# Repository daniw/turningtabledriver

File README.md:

turningtabledriver
==================

Full bridge driver for a dc motor driving a turning table.

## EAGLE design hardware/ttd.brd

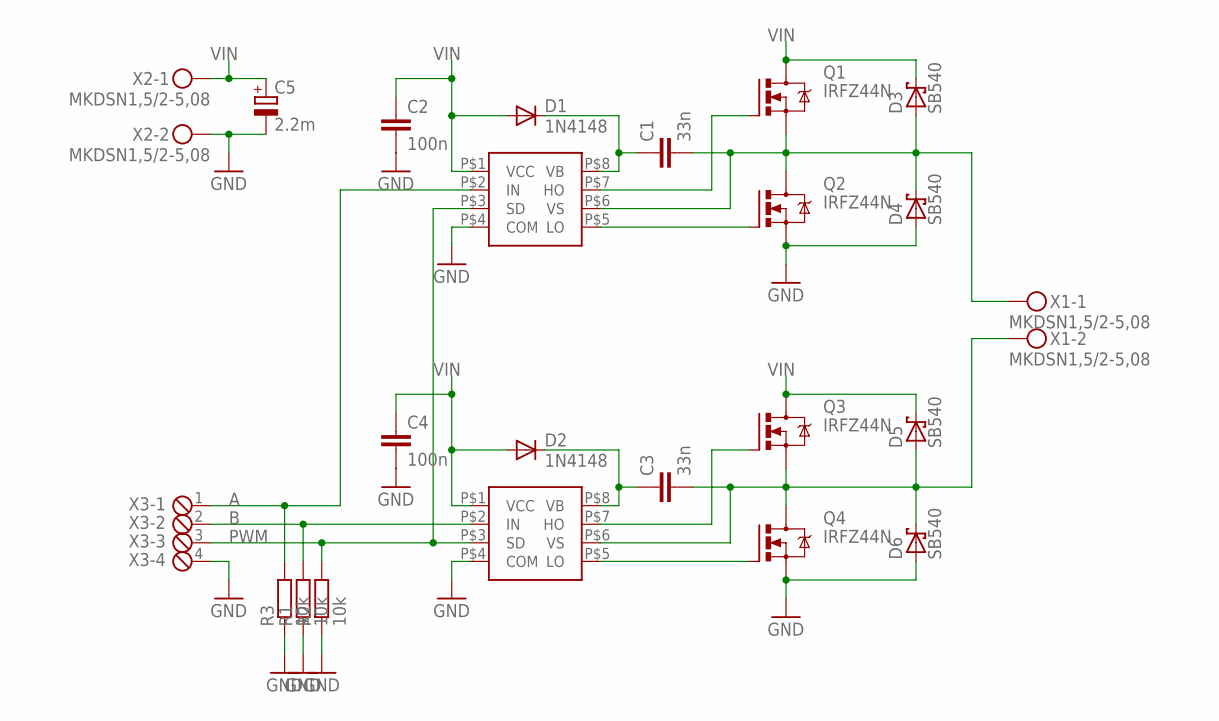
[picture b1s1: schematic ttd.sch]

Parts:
C1, C3: 33n; C050-025X075
C2, C4: 100n; C075-032X103
C5: 2.2m; E7,5-18
D1, D2: 1N4148; DO35-10
D3, D4, D5, D6: SB540; DO201T15
Q1, Q2, Q3, Q4: IRFZ44N; TO220BV
R1, R2: 10k; 0207/7
R3: 10k; 0207/10
U$1, U$2: IR2104; IR2104_DIL
X1, X2: MKDSN1,5/2-5,08
X3: MPT4; 4POL254

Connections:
A: R3.2, U$1.P$2 (IN), X3.1
B: R1.2, U$2.P$2 (IN), X3.2
GND: C2.2, C4.2, C5.-, D4.A, D6.A, Q2.S, Q4.S, R1.1, R2.1, R3.1, U$1.P$4 (COM), U$2.P$4 (COM), X2.2, X3.4
unnamed: Q2.G, U$1.P$5 (LO)
unnamed: Q4.G, U$2.P$5 (LO)
unnamed: Q1.G, U$1.P$7 (HO)
unnamed: C1.2, D3.A, D4.C, Q1.S, Q2.D, U$1.P$6 (VS), X1.1
unnamed: C1.1, D1.C, U$1.P$8 (VB)
unnamed: C3.2, D5.A, D6.C, Q3.S, Q4.D, U$2.P$6 (VS), X1.2
unnamed: Q3.G, U$2.P$7 (HO)
unnamed: C3.1, D2.C, U$2.P$8 (VB)
PWM: R2.2, U$1.P$3 (SD), U$2.P$3 (SD), X3.3
VIN: C2.1, C4.1, C5.+, D1.A, D2.A, D3.C, D5.C, Q1.D, Q3.D, U$1.P$1 (VCC), U$2.P$1 (VCC), X2.1

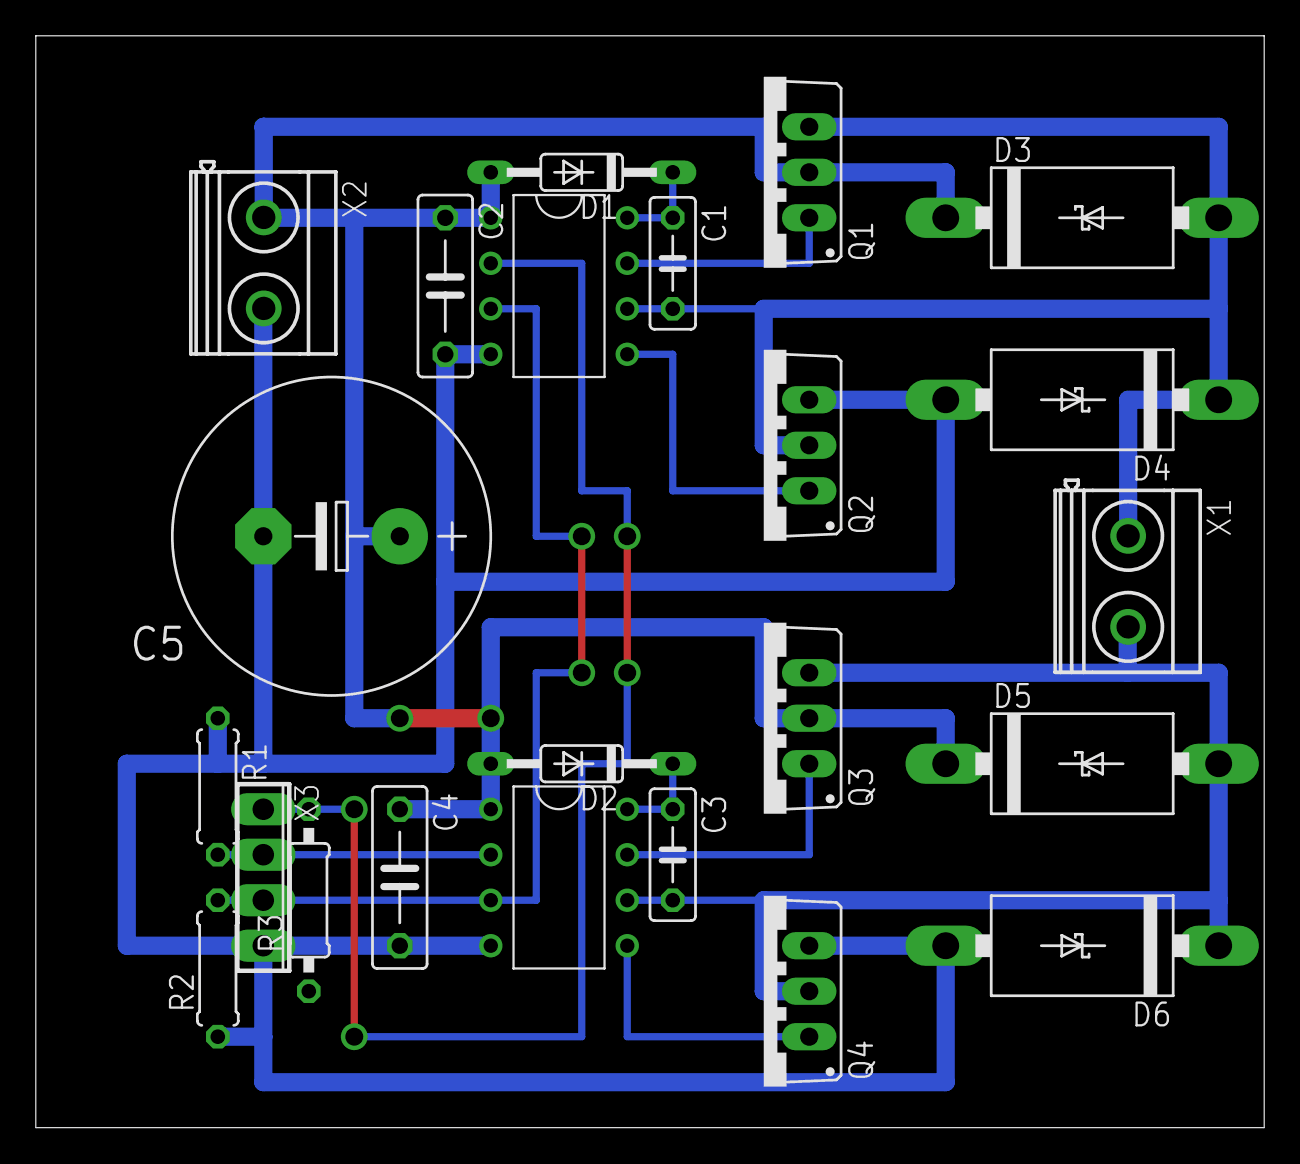
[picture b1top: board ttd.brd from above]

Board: 2 copper layers, 68.6 x 61.0 mm, 23 parts (0 on the bottom side), 13 nets.

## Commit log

2013-10-23 .gitignore
2013-10-23 Datasheet
2013-10-23 .gitignore prepared for hardware
2013-10-23 Schematic started
2013-10-26 Schottkydioden eingefügt
2013-10-26 Stecker eingefügt
2013-10-26 Netzklassen definiert
2013-10-26 Layout
2013-10-26 Elektrolytkondensator eingefügt
2013-10-26 Transistoren weiter auseinander geschoben für mehr Platz für Kühlkörper
2013-10-27 Gitter
2013-10-27 kleine Verschiebungen
2013-10-27 Ordner für Firmware vorbereitet
2013-10-27 Änderungen beim Aufbau im Layout nachgetragen, Bauteilwerte eingetragen
